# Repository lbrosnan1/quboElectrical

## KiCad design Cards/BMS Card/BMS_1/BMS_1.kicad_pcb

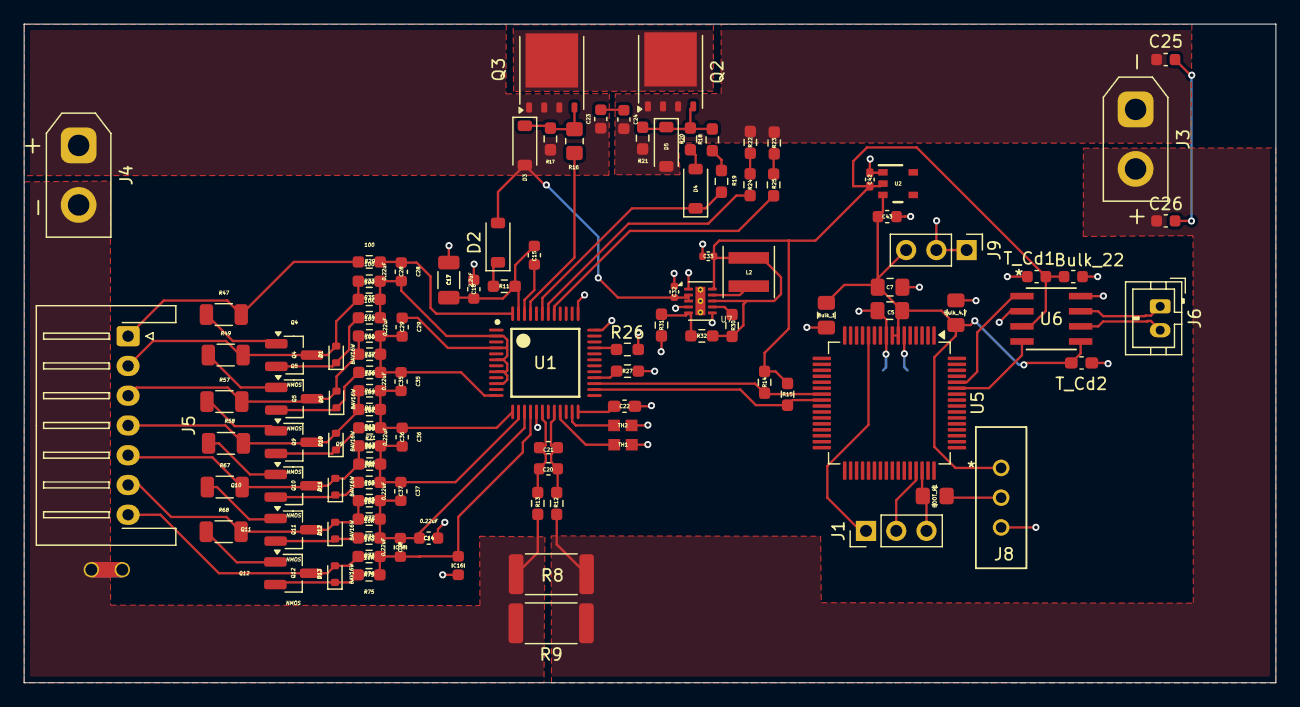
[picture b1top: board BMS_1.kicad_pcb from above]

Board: 2 copper layers, 105.1 x 55.3 mm, 111 parts (1 on the bottom side), 70 nets.

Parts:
BOOT_R1: 10k; R_0805_2012Metric_Pad1.20x1.40mm_HandSolder
Bulk_1: 1uF; C_0805_2012Metric_Pad1.18x1.45mm_HandSolder
Bulk_4.7: 4.7uF; C_0805_2012Metric_Pad1.18x1.45mm_HandSolder
Bulk_22: 22uF; C_0603_1608Metric
C5, C6, C7: 100nF; C_0805_2012Metric_Pad1.18x1.45mm_HandSolder
C14, C16, C28, C29, C35, C36, C37, C38: 0.22uF; C_0603_1608Metric
C15: 0.47uF; C_0603_1608Metric
C17: 2.2uF; C_1206_3216Metric
C18, C21: 100pF; C_0603_1608Metric
C20, C23, C24, C25, C26: 0.1uF; C_0603_1608Metric
C22: 2.2uF; C_0603_1608Metric_Pad1.08x0.95mm_HandSolder
C32: 2.2uF; C_0402_1005Metric
C33: 22uF; C_0402_1005Metric
C42: 0.1uF; C_0402_1005Metric_Pad0.74x0.62mm_HandSolder
C43: 1uF; C_0603_1608Metric
D1, D6, D10, D11, D12, D13: BAV16W; D_SOD-523
D2: BAV16W; D_SOD-123
D3, D5: 16V MMSZ5246B-7-F; D_SOD-123
D4: 100V; D_SOD-123
J1, J9: Conn_01x03_Pin; PinHeader_1x03_P2.54mm_Vertical
J3: Conn_01x02; AMASS_XT30UPB-M_1x02_P5.0mm_Vertical
J4: Conn_01x02; AMASS_XT30UPB-F_1x02_P5.0mm_Vertical
J5: Conn_01x07; JST_XH_S7B-XH-A-1_1x07_P2.50mm_Horizontal
J6: Conn_01x02; JST_PH_B2B-PH-K_1x02_P2.00mm_Vertical
J8: Conn_01x03; slide_switch_EGER1218_Thruster
L2: 10uH; L_Coilcraft_XxL4040
NT1: NetTie_2; NetTie-2_THT_Pad1.0mm
Q2, Q3: CSD17327Q5A; TDSON-8-1
Q4, Q5, Q9, Q10, Q11, Q12: NMOS; SOT-23_Handsoldering
R8, R9: 0.004; R_2512_6332Metric
R11, R12, R13, R29, R33, R35, R37, R61, R62, R64, R66, R71, R72, R74, R76: 100; R_0603_1608Metric_Pad0.98x0.95mm_HandSolder
R14, R15: 4.7k; R_0603_1608Metric_Pad0.98x0.95mm_HandSolder
R16: 5.1k; R_0805_2012Metric_Pad1.20x1.40mm_HandSolder
R17, R21: 10M; R_0603_1608Metric_Pad0.98x0.95mm_HandSolder
R18, R19, R20, R22, R23, R24, R25: 5.1k; R_0603_1608Metric_Pad0.98x0.95mm_HandSolder
R26, R27: 1K; R_0603_1608Metric_Pad0.98x0.95mm_HandSolder
R30, R34, R36, R63, R65, R73, R75: 10K; R_0603_1608Metric_Pad0.98x0.95mm_HandSolder
R31: 3.5K; R_0603_1608Metric_Pad0.98x0.95mm_HandSolder
R32: 2M; R_0603_1608Metric_Pad0.98x0.95mm_HandSolder
R47, R49, R57, R58, R67, R68: 25; R_1206_3216Metric
TH1, TH2: Thermistor_NTC_US; THRMC1608X95N
T_Cd1: 100nF; C_0603_1608Metric
T_Cd2: 100nF; C_0603_1608Metric_Pad1.08x0.95mm_HandSolder
U1: PBQ76942PFBT; PFB0048A_L
U2: TLV70430DBVR; DBV0005A_L
U5: STM32G0B1RETx; LQFP-64_10x10mm_P0.5mm
U6: ATA6561-GAQW-N; SOIC8_4P9X3P9MC_MCH
U7: TPS62175DQCR; WSON-10-1EP_2x3mm_P0.5mm_EP0.84x2.4mm_ThermalVias

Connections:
3.3v: Bulk_1.2, Bulk_4.7.1, C5.1, C7.1, C43.2, J8.1, J9.3, T_Cd2.1, U2.3 (OUT), U5.7 (VREF+), U5.8 (VDD), U6.5 (VIO)
5V: Bulk_22.1, C33.1, C42.1, L2.2, R14.2, R15.2, R30.1, R32.1, T_Cd1.1, U2.2 (IN), U6.3 (VCC), U7.8 (SLEEP), U7.10 (VOS)
/NRST: J1.1, U5.12 (PF2)
/SWCLK: BOOT_R1.1, J1.3, U5.46 (PA14)
/SWDIO: J1.2, U5.45 (PA13)
BAT+: C23.2, C32.1, D2.2 (A), D3.2 (A), J4.1, Q3.1 (S), Q3.2 (S), Q3.3 (S), R17.1, U7.2 (VIN), U7.3 (EN)
BAT-: J4.2, NT1.2, R8.2, R9.2, R13.2
CAN+: J6.1, U6.7 (CANH)
CAN-: J6.2, U6.6 (CANL)
CHG: R16.2, U1.45 (CHG)
Cell 1: D12.2 (A), J5.6, Q11.3 (S), R68.2, R72.2, R74.2
Cell 2: D11.2 (A), J5.5, Q10.3 (S), R66.2, R67.2, R71.2
Cell 3: D10.2 (A), J5.4, Q9.3 (S), R58.2, R62.2, R64.2
Cell 4: D6.2 (A), J5.3, Q5.3 (S), R37.2, R57.2, R61.2
Cell 5: D1.2 (A), J5.2, Q4.3 (S), R33.2, R35.2, R49.2
Cell 6: J5.1, R29.2, R47.2
Cell (Stack Bottom): D13.2 (A), J5.7, Q12.3 (S), R76.2
DSG: D4.1 (K), R19.2, U1.43 (DSG)
FDCAN_RX: U5.59 (PB5), U6.4 (RXD)
FDCAN_TX: U5.60 (PB6), U6.1 (TXD)
GND: Bulk_1.1, Bulk_4.7.2, Bulk_22.2, C5.2, C6.1, C7.2, C14.1, C16.2, C17.2, C18.1, C22.2, C32.2, C33.2, C42.2, C43.1, J8.3, J9.1, J9.2, NT1.1, R26.2, R27.2, R31.1, TH1.1, TH2.2, T_Cd1.2, T_Cd2.2, U1.17 (VSS), U1.36 (REGIN), U1.37 (BREG), U2.1 (GND), U5.9 (VSS), U6.2 (GND), U6.8 (STBY), U7.1 (PGND), U7.4 (NC), U7.6 (AGND), U7.11 (PAD)
LD: R25.1, U1.41 (LD)
unnamed: C23.1, C24.2
unnamed: C25.1, C26.2
unnamed: D1.1 (K), Q4.2 (G), R34.2
unnamed: D2.1 (K), R11.2
unnamed: D3.1 (K), Q3.4 (G), R16.1, R17.2
unnamed: D4.2 (A), R20.2
unnamed: D5.1 (K), Q2.4 (G), R18.1, R20.1, R21.2
unnamed: D6.1 (K), Q5.2 (G), R36.2
unnamed: D10.1 (K), Q9.2 (G), R63.2
unnamed: D11.1 (K), Q10.2 (G), R65.2
unnamed: D12.1 (K), Q11.2 (G), R73.2
unnamed: D13.1 (K), Q12.2 (G), R75.2
unnamed: BOOT_R1.2, J8.2
unnamed: Q4.1 (D), R47.1
unnamed: Q5.1 (D), R49.1
unnamed: Q9.1 (D), R57.1
unnamed: Q10.1 (D), R58.1
unnamed: Q11.1 (D), R67.1
unnamed: Q12.1 (D), R68.1
unnamed: R18.2, R19.1
unnamed: R22.1, R24.2
unnamed: R23.1, R25.2
unnamed: C15.1, C17.1, C18.2, R11.1, U1.47 (BAT)
unnamed: C15.2, U1.46 (CP1)
unnamed: R27.1, U1.28 (HDQ)
unnamed: C22.1, U1.24 (REG18)
unnamed: R26.1, U1.33 (RST_SHUT)
unnamed: TH1.2, U1.21 (TS1)
unnamed: TH2.1, U1.23 (TS3)
unnamed: C16.1, C38.2, R75.1, R76.1, U1.16 (VC0)
unnamed: C14.2, C37.2, C38.1, R72.1, R73.1, R74.1, U1.15 (VC1)
unnamed: C36.2, C37.1, R65.1, R66.1, R71.1, U1.14 (VC2)
unnamed: C35.2, C36.1, R62.1, R63.1, R64.1, U1.13 (VC3)
unnamed: C29.2, C35.1, R36.1, R37.1, R61.1, U1.12 (VC4)
unnamed: C28.2, C29.1, R33.1, R34.1, R35.1, U1.2 (VC9), U1.4 (VC8), U1.6 (VC7), U1.8 (VC6), U1.10 (VC5)
unnamed: C28.1, R29.1, U1.48 (VC10)
unnamed: R31.2, R32.2, U7.5 (FB)
unnamed: R30.2, U7.7 (PG)
unnamed: L2.1, U7.9 (SW)
PACK: R24.1, U1.42 (PACK)
PACK+: C24.1, C25.2, D5.2 (A), J3.1, Q2.1 (S), Q2.2 (S), Q2.3 (S), R21.1, R22.2, R23.2
PACK-: C26.1, J3.2, R8.1, R9.1, R12.2
Q_D: Q2.5 (D), Q3.5 (D)
SCL: R15.1, U1.26 (SCL), U5.24 (PA7)
SDA: R14.1, U1.27 (SDA), U5.23 (PA6)
SRN: C20.2, C21.1, R12.1, U1.20 (SRN)
SRP: C20.1, C21.2, R13.1, U1.18 (SRP)
VBAT: C6.2, U5.6 (VBAT)

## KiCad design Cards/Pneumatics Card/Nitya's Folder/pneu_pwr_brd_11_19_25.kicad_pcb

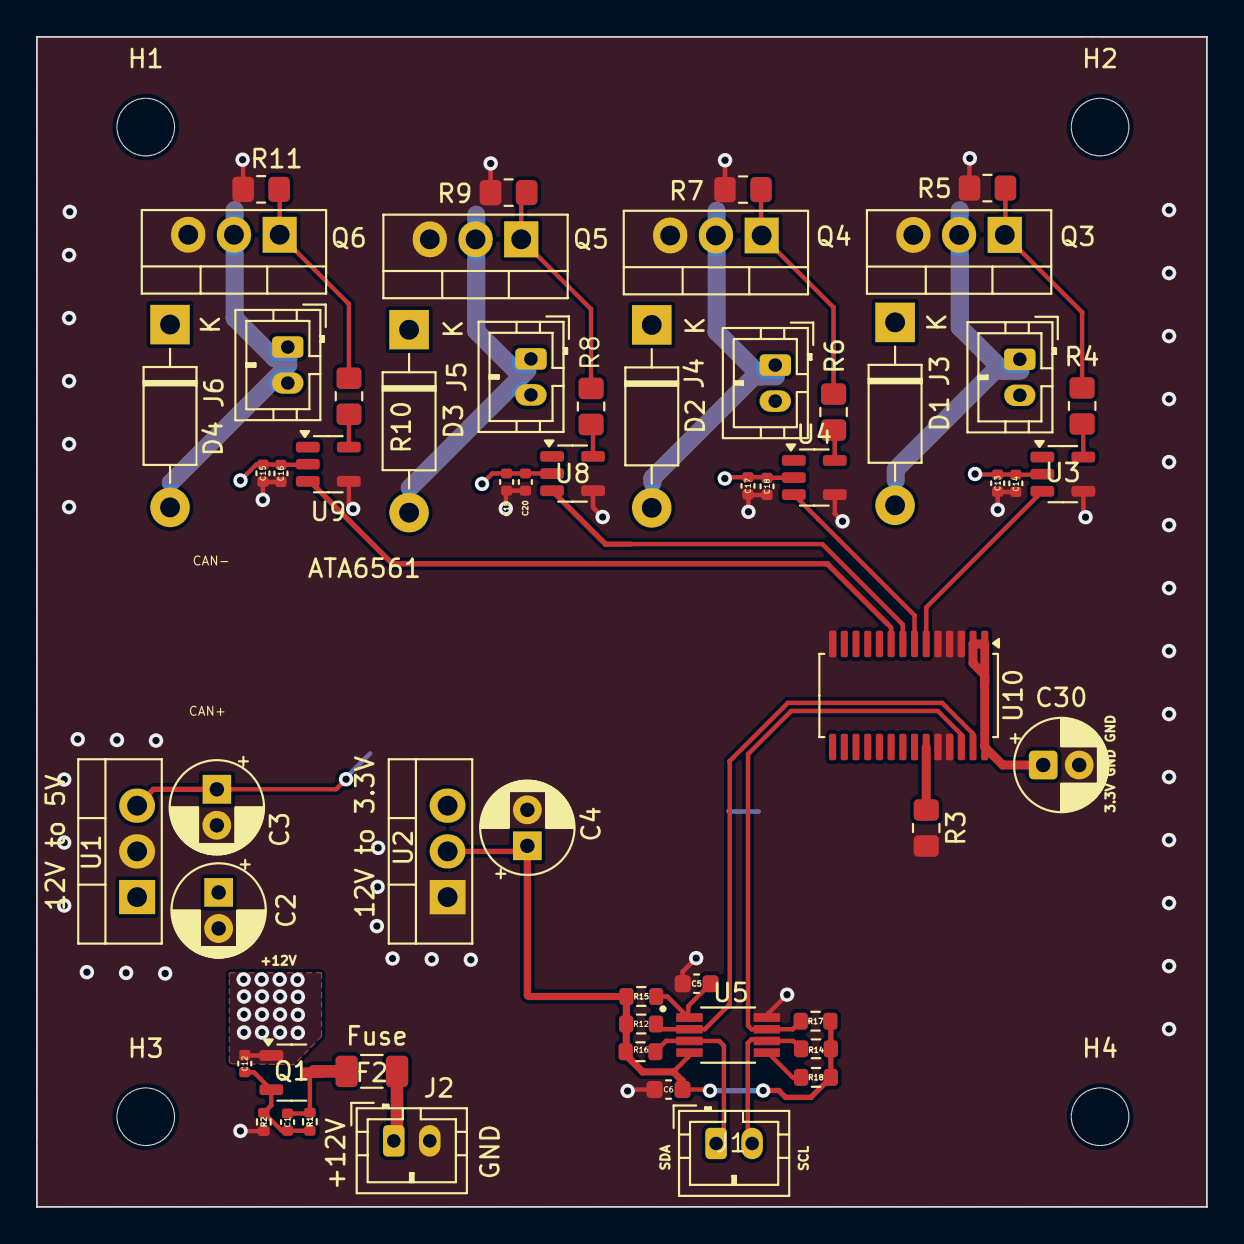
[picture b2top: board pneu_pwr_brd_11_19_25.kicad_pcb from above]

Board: 4 copper layers, 65.0 x 65.0 mm, 61 parts (0 on the bottom side), 31 nets.

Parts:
C1: 22nF; C_0402_1005Metric
C2, C3, C4, C30: 10u; CP_Radial_D5.0mm_P2.00mm
C5, C6: 0.1u; C_0603_1608Metric
C12: 0.47u; C_0402_1005Metric
C13, C16, C18, C20: 1uF; C_0402_1005Metric
C14, C15, C17, C19: 0.1uF; C_0402_1005Metric
D1, D2, D3, D4: 1N47xxA; D_DO-41_SOD81_P10.16mm_Horizontal
F2: 10A; Fuse_1206_3216Metric
H1, H2, H3, H4: MountingHole; MountingHole_3.2mm_M3_DIN965
J1, J2, J3, J4, J5, J6: 2X1; JST_PH_B2B-PH-K_1x02_P2.00mm_Vertical
Q1: NTR0202PLT1G OR Si2347DS; SOT-23-3
Q3, Q4, Q5, Q6: FQP30N06L; TO-220-3_Vertical
R1: 4.7k; R_0402_1005Metric
R2: 1k; R_0402_1005Metric
R3, R5, R7, R9, R11: 10k; R_0805_2012Metric_Pad1.20x1.40mm_HandSolder
R4, R6, R8, R10: 330; R_0805_2012Metric_Pad1.20x1.40mm_HandSolder
R12, R14, R15, R16, R17, R18: 10k; R_0603_1608Metric
U1: L7805; TO-220-3_Vertical
U2: LD1117V33; TO-220-3_Vertical
U3, U4, U8, U9: MCP1416; SOT-23-5
U5: TCA4307; SOP65P490X110-8N
U10: PCA9685; TSSOP-28_4.4x9.7mm_P0.65mm

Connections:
3.3V: C4.1, C6.2, R12.2, R14.1, R15.1, R16.2, R17.1, R18.1, U2.2 (VO), U5.4 (VCC)
5V: C3.1, U1.3 (OUT)
12V: C2.1, C12.2, C13.2, C14.2, C15.2, C16.2, C17.2, C18.2, C19.2, C20.2, D1.1 (K), D2.1 (K), D3.1 (K), D4.1 (K), J3.1, J4.1, J5.1, J6.1, Q1.1 (D), U1.1 (IN), U2.3 (VI), U3.2 (Vdd), U4.2 (Vdd), U8.2 (Vdd), U9.2 (Vdd)
+5V: C30.1, U10.1 (A0), U10.2 (A1), U10.28 (VDD)
+12V_fuse: F2.1, J2.1
GND: C2.2, C3.2, C4.2, C5.1, C6.1, C13.1, C14.1, C15.1, C16.1, C17.1, C18.1, C19.1, C20.1, C30.2, J2.2, Q3.3 (S), Q4.3 (S), Q5.3 (S), Q6.3 (S), R2.1, R3.2, R5.1, R7.1, R9.1, R11.1, U1.2 (GND), U2.1 (GND), U3.4 (GND), U4.4 (GND), U5.8 (GND), U8.4 (GND), U9.4 (GND), U10.3 (A2), U10.4 (A3), U10.5 (A4), U10.14 (GND), U10.24 (A5), U10.25 (EXTCLK)
unnamed: C1.1, C12.1, Q1.2 (G), R1.1, R2.2
unnamed: C1.2, F2.2, Q1.3 (S), R1.2
unnamed: Q3.1 (G), R4.2, R5.2
unnamed: Q4.1 (G), R6.2, R7.2
unnamed: Q5.1 (G), R8.2, R9.2
unnamed: Q6.1 (G), R10.2, R11.2
unnamed: R4.1, U3.5 (OUT)
unnamed: R6.1, U4.5 (OUT)
unnamed: C5.2, R15.2, U5.1 (EN)
unnamed: R18.2, U5.5 (READY)
unnamed: R8.1, U8.5 (OUT)
unnamed: R10.1, U9.5 (OUT)
unnamed: R3.1, U10.23 (OE')
S1CTRL: U3.3 (IN), U10.6 (PWM0)
S2CTRL: U4.3 (IN), U10.7 (PWM1)
S3CTRL: U8.3 (IN), U10.8 (PWM2)
S4CTRL: U9.3 (IN), U10.9 (PWM3)
SCL: R17.2, U5.7 (SCLOUT), U10.26 (SCL)
SCL_ext: J1.2, R14.2, U5.6 (SCLIN)
SDA: R16.1, U5.2 (SDAOUT), U10.27 (SDA)
SDA_ext: J1.1, R12.1, U5.3 (SDAIN)
SLN1-: D1.2 (A), J3.2, Q3.2 (D)
SLN2-: D2.2 (A), J4.2, Q4.2 (D)
SLN3-: D3.2 (A), J5.2, Q5.2 (D)
SLN4-: D4.2 (A), J6.2, Q6.2 (D)

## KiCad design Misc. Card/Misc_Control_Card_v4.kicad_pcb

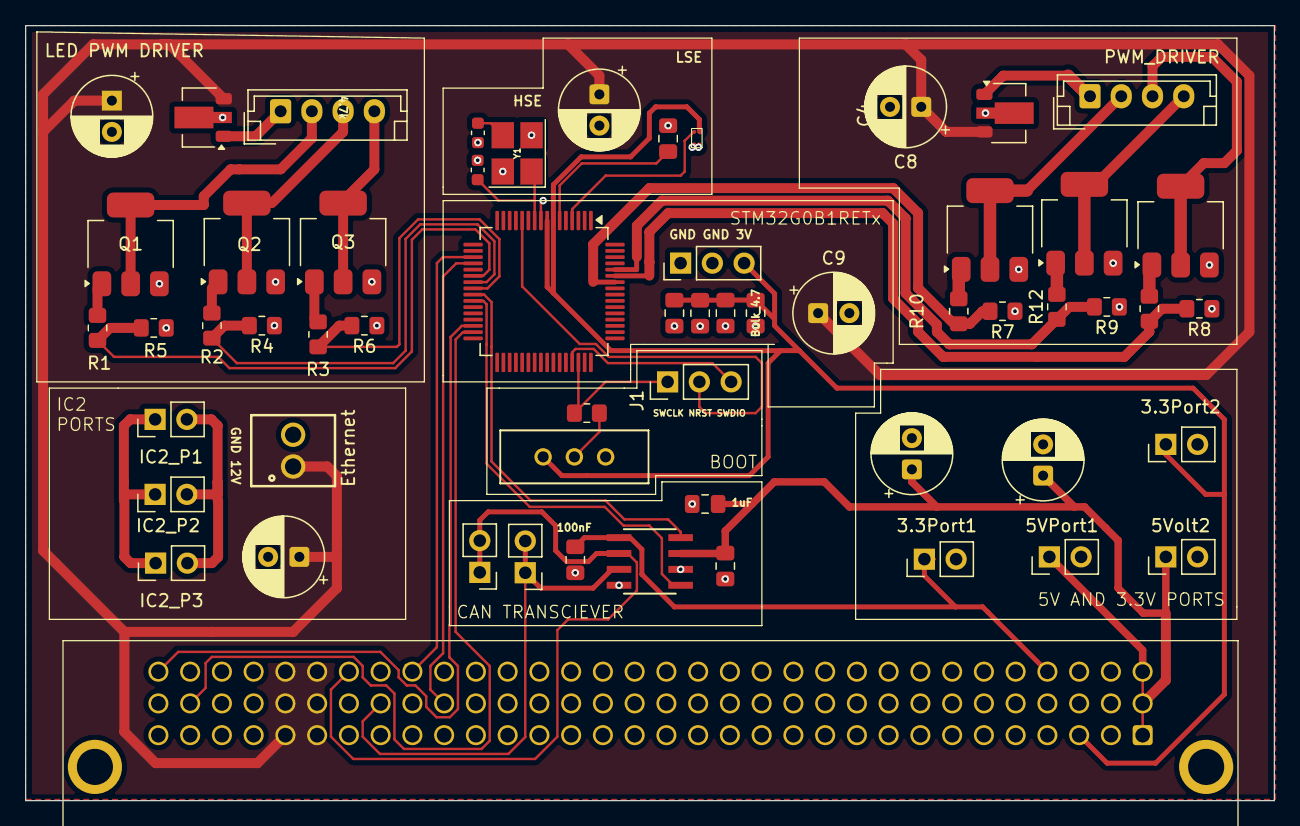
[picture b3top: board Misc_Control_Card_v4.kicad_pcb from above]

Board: 2 copper layers, 99.9 x 62.0 mm, 58 parts (0 on the bottom side), 42 nets.

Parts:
3.3Port1, 3.3Port2, 5VPort1, 5Volt2: Conn_01x02; PinHeader_1x02_P2.54mm_Vertical
BOOT_R1: 10k; R_0805_2012Metric_Pad1.20x1.40mm_HandSolder
Bulk_1: 1uF; C_0805_2012Metric_Pad1.18x1.45mm_HandSolder
Bulk_4.7: 4.7uF; C_0805_2012Metric_Pad1.18x1.45mm_HandSolder
Bulk_22: 22uF; C_0805_2012Metric_Pad1.18x1.45mm_HandSolder
C1, C8: 100nf; CP_Radial_D6.3mm_P2.50mm
C2, C3: 10pF; C_0603_1608Metric
C4, C9, C10: 100 µF; CP_Radial_D6.3mm_P2.50mm
C5, C6, C7: 100nF; C_0805_2012Metric_Pad1.18x1.45mm_HandSolder
C11, C12: 1 µF; CP_Radial_D6.3mm_P2.50mm
IC2_P1, IC2_P2, IC2_P3: Conn_01x02; PinHeader_1x02_P2.54mm_Vertical
J1, J9: Conn_01x03_Pin; PinHeader_1x03_P2.54mm_Vertical
J2: Conn_01x02; 6509475
J4, J5: Conn_01x02; PinHeader_1x02_P2.54mm_Vertical
J7: Screw_Terminal_01x02; screw_junc_254_2by1
J8: Conn_01x03; slide_switch_EGER1218_Thruster
LED_Connection1, LED_Connection2: Conn_01x04; JST_EH_B4B-EH-A_1x04_P2.50mm_Vertical
LED_DRIVER1: HV9923N8-G; SOT-89-3
PWM_DRIVER: HV9923N8-G; SOT-89-3
Q1, Q2, Q3, Q4, Q5, Q6: NDT3055L; SOT-223-3_TabPin2
R1, R2, R3, R10, R11, R12: 220; R_0805_2012Metric_Pad1.20x1.40mm_HandSolder
R4, R5, R6, R7, R8, R9: 10k; R_0805_2012Metric_Pad1.20x1.40mm_HandSolder
T_Cd1, T_Cd2: 100nF; C_0805_2012Metric_Pad1.18x1.45mm_HandSolder
U1: SiT1552
U5: STM32G0B1RETx; LQFP-64_10x10mm_P0.5mm
U6: ATA6561-GAQW-N; SOIC8_4P9X3P9MC_MCH
Y1: 16Mhz; Crystal_SMD_3225-4Pin_3.2x2.5mm_HandSoldering

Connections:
3.3v: 3.3Port1.1, 3.3Port2.1, Bulk_1.2, Bulk_4.7.1, C5.1, C7.1, J2.A3, J2.B3, J2.B4, J2.C4, J8.1, J9.3, T_Cd2.1, U1.3 (Vdd), U5.7 (VREF+), U5.8 (VDD), U6.5 (VIO)
5V: 5VPort1.1, 5Volt2.1, Bulk_22.1, C11.1, C12.1, J2.A1, J2.B1, J2.C1, T_Cd1.1, U6.3 (VCC)
12V: C1.1, C4.1, C8.1, C9.1, C10.1, J2.A27, J2.A28, J2.B27, J2.B28, J2.C27, J2.C28, J7.1, LED_DRIVER1.3 (VDD), PWM_DRIVER.3 (VDD)
/NRST: J1.2, U5.12 (PF2)
/SWCLK: BOOT_R1.1, J1.1, U5.46 (PA14)
/SWDIO: J1.3, U5.45 (PA13)
CAN+: J2.B25, J4.1, J4.2, U6.7 (CANH)
CAN-: J2.C26, J5.1, J5.2, U6.6 (CANL)
FDCAN_RX: U5.25 (PC4), U6.4 (RXD)
FDCAN_TX: U5.26 (PC5), U6.1 (TXD)
GND: 3.3Port1.2, 3.3Port2.2, 5VPort1.2, 5Volt2.2, Bulk_1.1, Bulk_4.7.2, Bulk_22.2, C1.2, C2.2, C3.2, C4.2, C5.2, C6.1, C7.2, C8.2, C9.2, C10.2, C11.2, C12.2, J2.A2, J2.A4, J2.A5, J2.A6, J2.A8, J2.A10, J2.A12, J2.A14, J2.A16, J2.A18, J2.A20, J2.A21, J2.A22, J2.A24, J2.A26, J2.A32, J2.B2, J2.B5, J2.B6, J2.B21, J2.B22, J2.C2, J2.C3, J2.C5, J2.C6, J2.C7, J2.C9, J2.C11, J2.C13, J2.C15, J2.C17, J2.C19, J2.C21, J2.C22, J2.C23, J2.C25, J2.C31, J7.2, J8.3, J9.1, J9.2, LED_DRIVER1.2 (GND), PWM_DRIVER.2 (GND), Q1.3 (S), Q2.3 (S), Q3.3 (S), Q4.3 (S), Q5.3 (S), Q6.3 (S), R4.1, R5.1, R6.1, R7.1, R8.1, R9.1, T_Cd1.2, T_Cd2.2, U1.1 (GND), U1.4 (GND), U5.9 (VSS), U6.2 (GND), U6.8 (STBY), Y1.2, Y1.4
IC2_JETSON+: IC2_P1.1, IC2_P2.1, IC2_P3.1
IC2_JETSON-: IC2_P1.2, IC2_P2.2, IC2_P3.2
unnamed: BOOT_R1.2, J8.2
unnamed: LED_Connection1.1, LED_DRIVER1.1 (D)
unnamed: LED_Connection1.2, Q1.2 (D)
unnamed: LED_Connection1.3, Q2.2 (D)
unnamed: LED_Connection1.4, Q3.2 (D)
unnamed: LED_Connection2.1, PWM_DRIVER.1 (D)
unnamed: LED_Connection2.2, Q4.2 (D)
unnamed: LED_Connection2.3, Q5.2 (D)
unnamed: LED_Connection2.4, Q6.2 (D)
unnamed: Q1.1 (G), R1.2
unnamed: Q2.1 (G), R2.2
unnamed: Q3.1 (G), R3.2
unnamed: Q4.1 (G), R10.2
unnamed: Q5.1 (G), R11.2
unnamed: Q6.1 (G), R12.2
PWM_1_Audio: R7.2, R10.1, U5.58 (PB4)
PWM_2_Audio: R8.2, R11.1, U5.59 (PB5)
PWM_3_Audio: R9.2, R12.1, U5.60 (PB6)
PWM_B_OUT: R1.1, R5.2, U5.22 (PA5)
PWM_G_OUT: R3.1, R6.2, U5.24 (PA7)
PWM_R_OUT: R2.1, R4.2, U5.23 (PA6)
RCC_OSC32_IN: U1.2 (CLK_Out), U5.4 (PC14)
RCC_OSC_IN: C2.1, U5.10 (PF0), Y1.1
RCC_OSC_OUT: C3.1, Y1.3
SCL_IN: J2.B32, J2.C32, U5.30 (PB10)
SDA_IN: J2.A31, J2.B31, U5.31 (PB11)
USART1+: J2.C24, U5.19 (PA2)
USART1-: J2.B23, U5.20 (PA3)
VBAT: C6.2, U5.6 (VBAT)

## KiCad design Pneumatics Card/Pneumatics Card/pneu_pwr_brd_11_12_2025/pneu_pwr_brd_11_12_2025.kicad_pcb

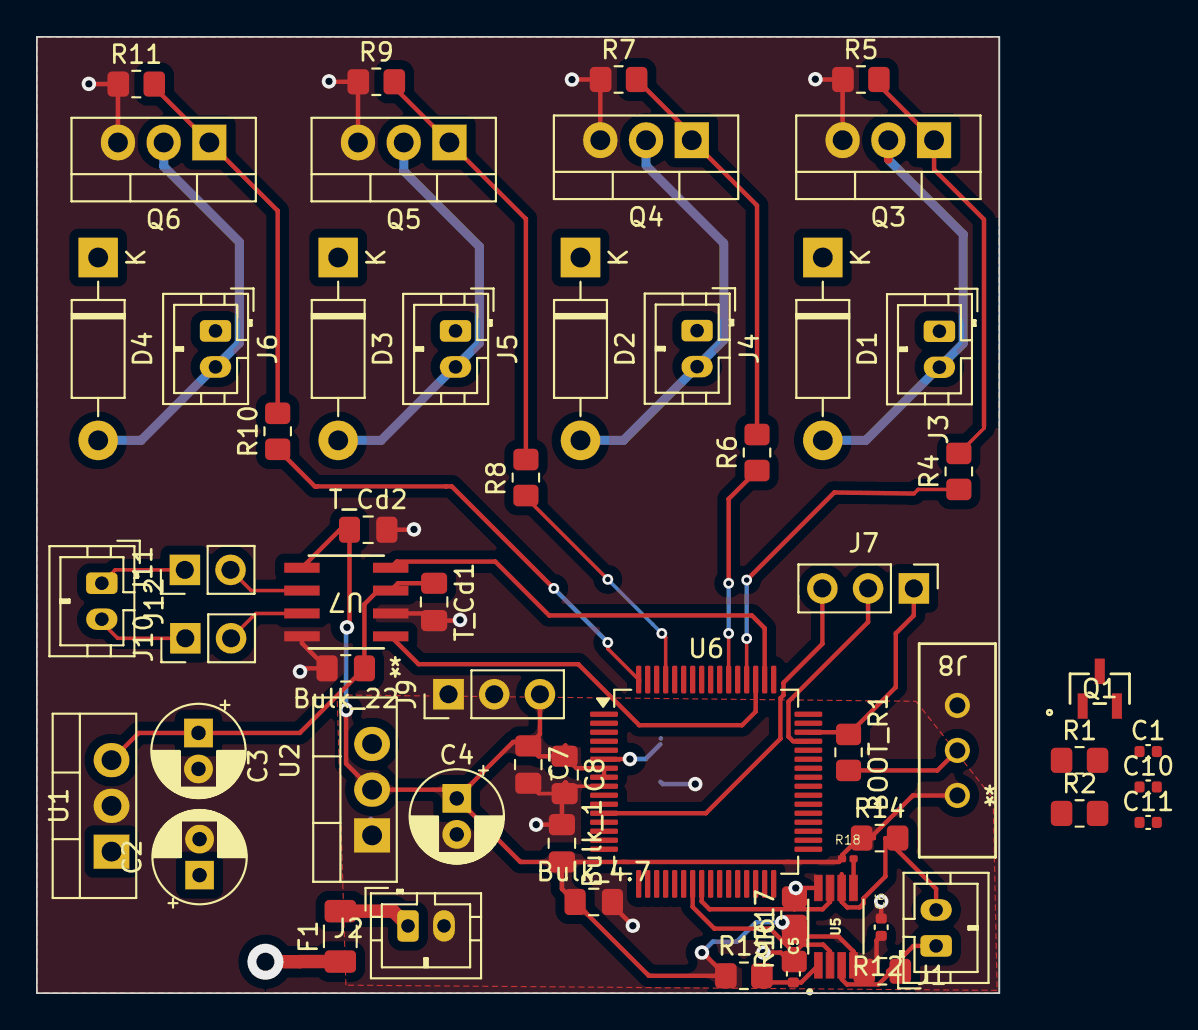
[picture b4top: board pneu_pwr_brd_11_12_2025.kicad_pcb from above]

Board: 4 copper layers, 53.5 x 53.1 mm, 60 parts (1 on the bottom side), 34 nets.

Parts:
BOOT_R1: 10k; R_0805_2012Metric_Pad1.20x1.40mm_HandSolder
Bulk_1: 1uF; C_0805_2012Metric_Pad1.18x1.45mm_HandSolder
Bulk_4.7: 4.7uF; C_0805_2012Metric_Pad1.18x1.45mm_HandSolder
Bulk_22: 22uF; C_0805_2012Metric_Pad1.18x1.45mm_HandSolder
C1, C10, C11: 4.7u; C_0402_1005Metric
C2, C3, C4: 10u; CP_Radial_D5.0mm_P2.00mm
C5, C6: 0.1u; C_0402_1005Metric
C7, C8, C9: 100nF; C_0805_2012Metric_Pad1.18x1.45mm_HandSolder
D1, D2, D3, D4: 1N47xxA; D_DO-41_SOD81_P10.16mm_Horizontal
F1: 10A; Fuse_1206_3216Metric
J1, J2, J3, J4, J5, J6, J12: 2X1; JST_PH_B2B-PH-K_1x02_P2.00mm_Vertical
J7, J9: Conn_01x03_Pin; PinHeader_1x03_P2.54mm_Vertical
J8: Conn_01x03; slide_switch_EGER1218_Thruster
J10, J11: Conn_01x02; PinHeader_1x02_P2.54mm_Vertical
Q1: NTR0202PLT1G; SOT-23_ONS
Q3, Q4, Q5, Q6: FQP30N06L; TO-220-3_Vertical
R1: 47k; R_0805_2012Metric_Pad1.20x1.40mm_HandSolder
R2: 100; R_0805_2012Metric_Pad1.20x1.40mm_HandSolder
R4, R6, R8, R10: 330; R_0805_2012Metric_Pad1.20x1.40mm_HandSolder
R5, R7, R9, R11, R12, R14, R15, R16, R17: 10k; R_0805_2012Metric_Pad1.20x1.40mm_HandSolder
R18: 10k; C_0201_0603Metric
T_Cd1, T_Cd2: 100nF; C_0805_2012Metric_Pad1.18x1.45mm_HandSolder
U1: L7805; TO-220-3_Vertical
U2: LD1117V33; TO-220-3_Vertical
U5: TCA4307; SOP65P490X110-8N
U6: STM32G0B1RETx; LQFP-64_10x10mm_P0.5mm
U7: ATA6561-GAQW-N; SOIC8_4P9X3P9MC_MCH

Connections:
3.3V: Bulk_1.2, Bulk_4.7.1, C4.1, C6.2, C7.1, C8.1, J8.1, J9.3, R12.2, R14.1, R15.1, R16.2, R17.1, R18.1, T_Cd2.1, U2.2 (VO), U5.4 (VCC), U6.7 (VREF+), U6.8 (VDD), U7.5 (VIO)
5V: Bulk_22.1, C3.1, T_Cd1.1, U1.3 (OUT), U7.3 (VCC)
12V: C2.1, C10.2, C11.2, D1.1 (K), D2.1 (K), D3.1 (K), D4.1 (K), J3.1, J4.1, J5.1, J6.1, Q1.1 (D), U1.1 (IN), U2.3 (VI)
+12V_fuse: F1.1, J2.1
/NRST: J7.3, U6.12 (PF2)
/SWCLK: BOOT_R1.1, J7.1, U6.46 (PA14)
/SWDIO: J7.2, U6.45 (PA13)
CAN+: J10.1, J10.2, J12.2, U7.7 (CANH)
CAN-: J11.1, J11.2, J12.1, U7.6 (CANL)
FDCAN_RX: U6.50 (PD0), U7.4 (RXD)
FDCAN_TX: U6.51 (PD1), U7.1 (TXD)
GND: Bulk_1.1, Bulk_4.7.2, Bulk_22.2, C2.2, C3.2, C4.2, C5.1, C6.1, C7.2, C8.2, C9.1, C11.1, J2.2, J8.3, J9.1, J9.2, Q3.3 (S), Q4.3 (S), Q5.3 (S), Q6.3 (S), R2.1, R5.1, R7.1, R9.1, R11.1, T_Cd1.2, T_Cd2.2, U1.2 (GND), U2.1 (GND), U5.8 (GND), U6.9 (VSS), U7.2 (GND), U7.8 (STBY)
unnamed: BOOT_R1.2, J8.2
unnamed: C1.1, C10.1, Q1.2 (G), R1.1, R2.2
unnamed: C1.2, F1.2, Q1.3 (S), R1.2
unnamed: Q3.1 (G), R4.2, R5.2
unnamed: Q4.1 (G), R6.2, R7.2
unnamed: Q5.1 (G), R8.2, R9.2
unnamed: Q6.1 (G), R10.2, R11.2
unnamed: C5.2, R15.2, U5.1 (EN)
unnamed: R18.2, U5.5 (READY)
S1CTRL: R4.1, U6.52 (PD2)
S2CTRL: R6.1, U6.54 (PD4)
S3CTRL: R8.1, U6.61 (PB7)
S4CTRL: R10.1, U6.64 (PC10)
SCL: R17.2, U5.7 (SCLOUT), U6.24 (PA7)
SCL_ext: J1.2, R14.2, U5.6 (SCLIN)
SDA: R16.1, U5.2 (SDAOUT), U6.23 (PA6)
SDA_ext: J1.1, R12.1, U5.3 (SDAIN)
SLN1-: D1.2 (A), J3.2, Q3.2 (D)
SLN2-: D2.2 (A), J4.2, Q4.2 (D)
SLN3-: D3.2 (A), J5.2, Q5.2 (D)
SLN4-: D4.2 (A), J6.2, Q6.2 (D)
VBAT: C9.2, U6.6 (VBAT)

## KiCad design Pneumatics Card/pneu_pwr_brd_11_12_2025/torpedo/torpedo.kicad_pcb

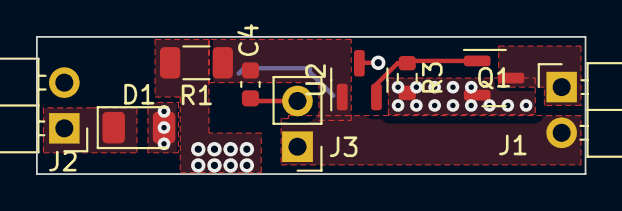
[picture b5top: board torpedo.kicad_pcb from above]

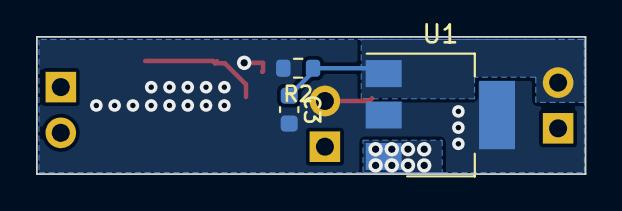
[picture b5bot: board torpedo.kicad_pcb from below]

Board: 2 copper layers, 30.5 x 7.6 mm, 12 parts (3 on the bottom side), 7 nets.

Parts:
C3: 1u; C_0603_1608Metric
C4: 10n; C_0603_1608Metric
D1: SD1206S100S1R0; D_1206_3216Metric
J1: Motor; PinHeader_1x02_P2.54mm_Horizontal
J2: Battery; PinHeader_1x02_P2.54mm_Horizontal
J3: Capacitors; PinHeader_1x02_P2.54mm_Vertical
Q1: DMG2301L; SOT-23
R1: 10; R_1206_3216Metric
R2, R3: 10k; R_0603_1608Metric
U1: LM340-5.0; SOT-223-3_TabPin2
U2: AH372X; SOT-23

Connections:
+6V: C4.1, J1.2, J3.1, R1.1, U2.1 (VDD)
GND: C3.2, C4.2, D1.2 (A), J3.2, Q1.2 (S), R2.2, R3.2, U1.2 (GND), U2.3 (GND)
unnamed: D1.1 (K), J2.1
unnamed: J1.1, Q1.3 (D)
unnamed: C3.1, J2.2, R2.1, U1.1 (VI)
unnamed: R1.2, U1.3 (VO)
SW: Q1.1 (G), R3.1, U2.2 (Output)
